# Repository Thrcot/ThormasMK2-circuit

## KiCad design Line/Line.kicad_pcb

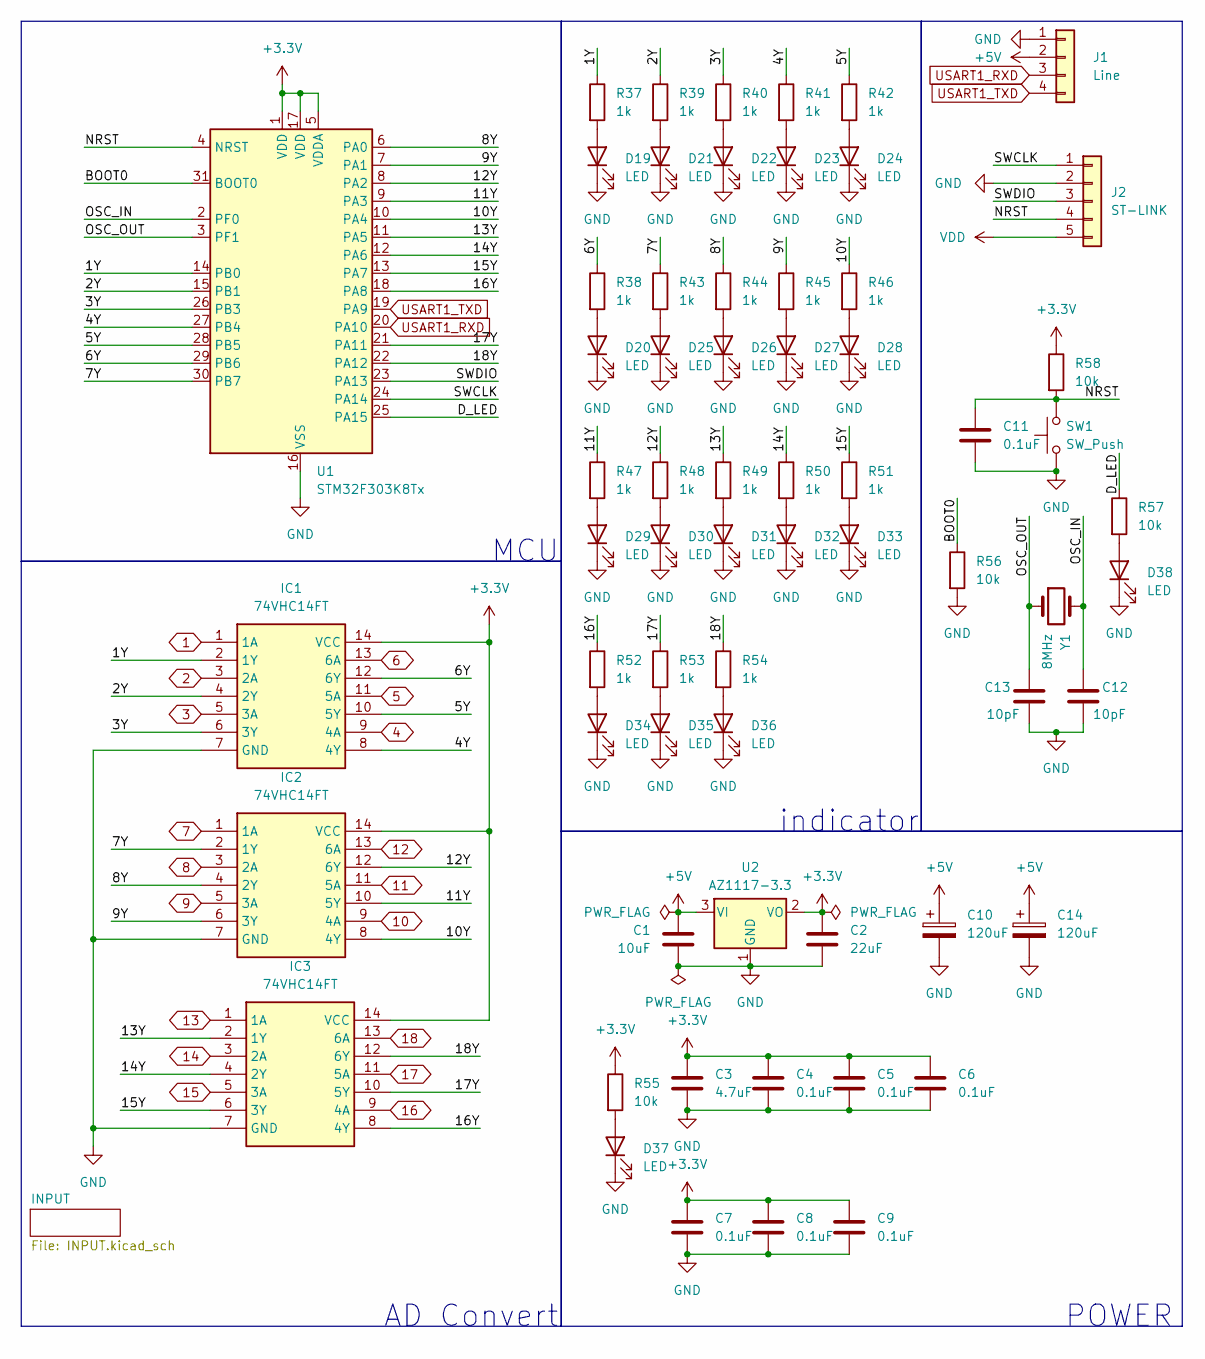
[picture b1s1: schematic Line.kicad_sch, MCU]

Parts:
C1: 10uF; C_0603_1608Metric
C2: 22uF; C_0603_1608Metric
C3: 4.7uF; C_0603_1608Metric
C4, C5, C6, C7, C8, C9, C11: 0.1uF; C_0402_1005Metric
C10, C14: 120uF; CP_Radial_D10.0mm_P5.00mm
C12, C13: 10pF; C_0402_1005Metric
D19, D20, D21, D22, D23, D24, D25, D26, D27, D28, D29, D30, D31, D32, D33, D34, D35, D36, D37, D38: LED; LED_0603_1608Metric
IC1, IC2, IC3: 74VHC14FT; SOP65P640X120-14N; Mouser Part Number 757-74VHC14FT
J1: Line; JST_XH_B4B-XH-A_1x04_P2.50mm_Vertical
J2: ST-LINK; PinHeader_1x05_P2.54mm_Vertical
R37, R38, R39, R40, R41, R42, R43, R44, R45, R46, R47, R48, R49, R50, R51, R52, R53, R54: 1k; R_0603_1608Metric
R55, R56, R57, R58: 10k; R_0603_1608Metric
SW1: SW_Push; SW_PUSH_6mm
U1: STM32F303K8Tx; LQFP-32_7x7mm_P0.8mm
U2: AZ1117-3.3; SOT-223-3_TabPin2
Y1: 8MHz; Crystal_HC49-4H_Vertical

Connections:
1: IC1.1 (1A); also elsewhere on the board
2: IC1.3 (2A); also elsewhere on the board
3: IC1.5 (3A); also elsewhere on the board
4: IC1.9 (4A); also elsewhere on the board
5: IC1.11 (5A); also elsewhere on the board
6: IC1.13 (6A); also elsewhere on the board
7: IC2.1 (1A); also elsewhere on the board
8: IC2.3 (2A); also elsewhere on the board
9: IC2.5 (3A); also elsewhere on the board
10: IC2.9 (4A); also elsewhere on the board
11: IC2.11 (5A); also elsewhere on the board
12: IC2.13 (6A); also elsewhere on the board
13: IC3.1 (1A); also elsewhere on the board
14: IC3.3 (2A); also elsewhere on the board
15: IC3.5 (3A); also elsewhere on the board
16: IC3.9 (4A); also elsewhere on the board
17: IC3.11 (5A); also elsewhere on the board
18: IC3.13 (6A); also elsewhere on the board
+3.3V: C2.1, C3.1, C4.1, C5.1, C6.1, C7.1, C8.1, C9.1, IC1.14 (VCC), IC2.14 (VCC), IC3.14 (VCC), R55.1, R58.1, U1.1 (VDD), U1.5 (VDDA), U1.17 (VDD), U2.2 (VO); also elsewhere on the board
+5V: C1.1, C10.1, C14.1, J1.2, U2.3 (VI)
/1Y: IC1.2 (1Y), R37.1, U1.14 (PB0)
/2Y: IC1.4 (2Y), R39.1, U1.15 (PB1)
/3Y: IC1.6 (3Y), R40.1, U1.26 (PB3)
/4Y: IC1.8 (4Y), R41.1, U1.27 (PB4)
/5Y: IC1.10 (5Y), R42.1, U1.28 (PB5)
/6Y: IC1.12 (6Y), R38.1, U1.29 (PB6)
/7Y: IC2.2 (1Y), R43.1, U1.30 (PB7)
/8Y: IC2.4 (2Y), R44.1, U1.6 (PA0)
/9Y: IC2.6 (3Y), R45.1, U1.7 (PA1)
/10Y: IC2.8 (4Y), R46.1, U1.10 (PA4)
/11Y: IC2.10 (5Y), R47.1, U1.9 (PA3)
/12Y: IC2.12 (6Y), R48.1, U1.8 (PA2)
/13Y: IC3.2 (1Y), R49.1, U1.11 (PA5)
/14Y: IC3.4 (2Y), R50.1, U1.12 (PA6)
/15Y: IC3.6 (3Y), R51.1, U1.13 (PA7)
/16Y: IC3.8 (4Y), R52.1, U1.18 (PA8)
/17Y: IC3.10 (5Y), R53.1, U1.21 (PA11)
/18Y: IC3.12 (6Y), R54.1, U1.22 (PA12)
/BOOT0: R56.1, U1.31 (BOOT0)
/D_LED: R57.1, U1.25 (PA15)
/NRST: C11.1, J2.4, R58.2, SW1.2, U1.4 (NRST)
/OSC_IN: C12.1, U1.2 (PF0), Y1.2
/OSC_OUT: C13.1, U1.3 (PF1), Y1.1
/SWCLK: J2.1, U1.24 (PA14)
/SWDIO: J2.3, U1.23 (PA13)
GND: C1.2, C2.2, C3.2, C4.2, C5.2, C6.2, C7.2, C8.2, C9.2, C10.2, C11.2, C12.2, C13.2, C14.2, D19.1 (K), D20.1 (K), D21.1 (K), D22.1 (K), D23.1 (K), D24.1 (K), D25.1 (K), D26.1 (K), D27.1 (K), D28.1 (K), D29.1 (K), D30.1 (K), D31.1 (K), D32.1 (K), D33.1 (K), D34.1 (K), D35.1 (K), D36.1 (K), D37.1 (K), D38.1 (K), IC1.7 (GND), IC2.7 (GND), IC3.7 (GND), J1.1, J2.2, R56.2, SW1.1, U1.16 (VSS), U1.32 (VSS), U2.1 (GND); also elsewhere on the board
unnamed: D19.2 (A), R37.2
unnamed: D20.2 (A), R38.2
unnamed: D21.2 (A), R39.2
unnamed: D22.2 (A), R40.2
unnamed: D23.2 (A), R41.2
unnamed: D24.2 (A), R42.2
unnamed: D25.2 (A), R43.2
unnamed: D26.2 (A), R44.2
unnamed: D27.2 (A), R45.2
unnamed: D28.2 (A), R46.2
unnamed: D29.2 (A), R47.2
unnamed: D30.2 (A), R48.2
unnamed: D31.2 (A), R49.2
unnamed: D32.2 (A), R50.2
unnamed: D33.2 (A), R51.2
unnamed: D34.2 (A), R52.2
unnamed: D35.2 (A), R53.2
unnamed: D36.2 (A), R54.2
unnamed: D37.2 (A), R55.2
unnamed: D38.2 (A), R57.2
USART1_RXD: J1.3, U1.20 (PA10)
USART1_TXD: J1.4, U1.19 (PA9)
VDD: J2.5

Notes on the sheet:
MCU
AD Convert
indicator
POWER

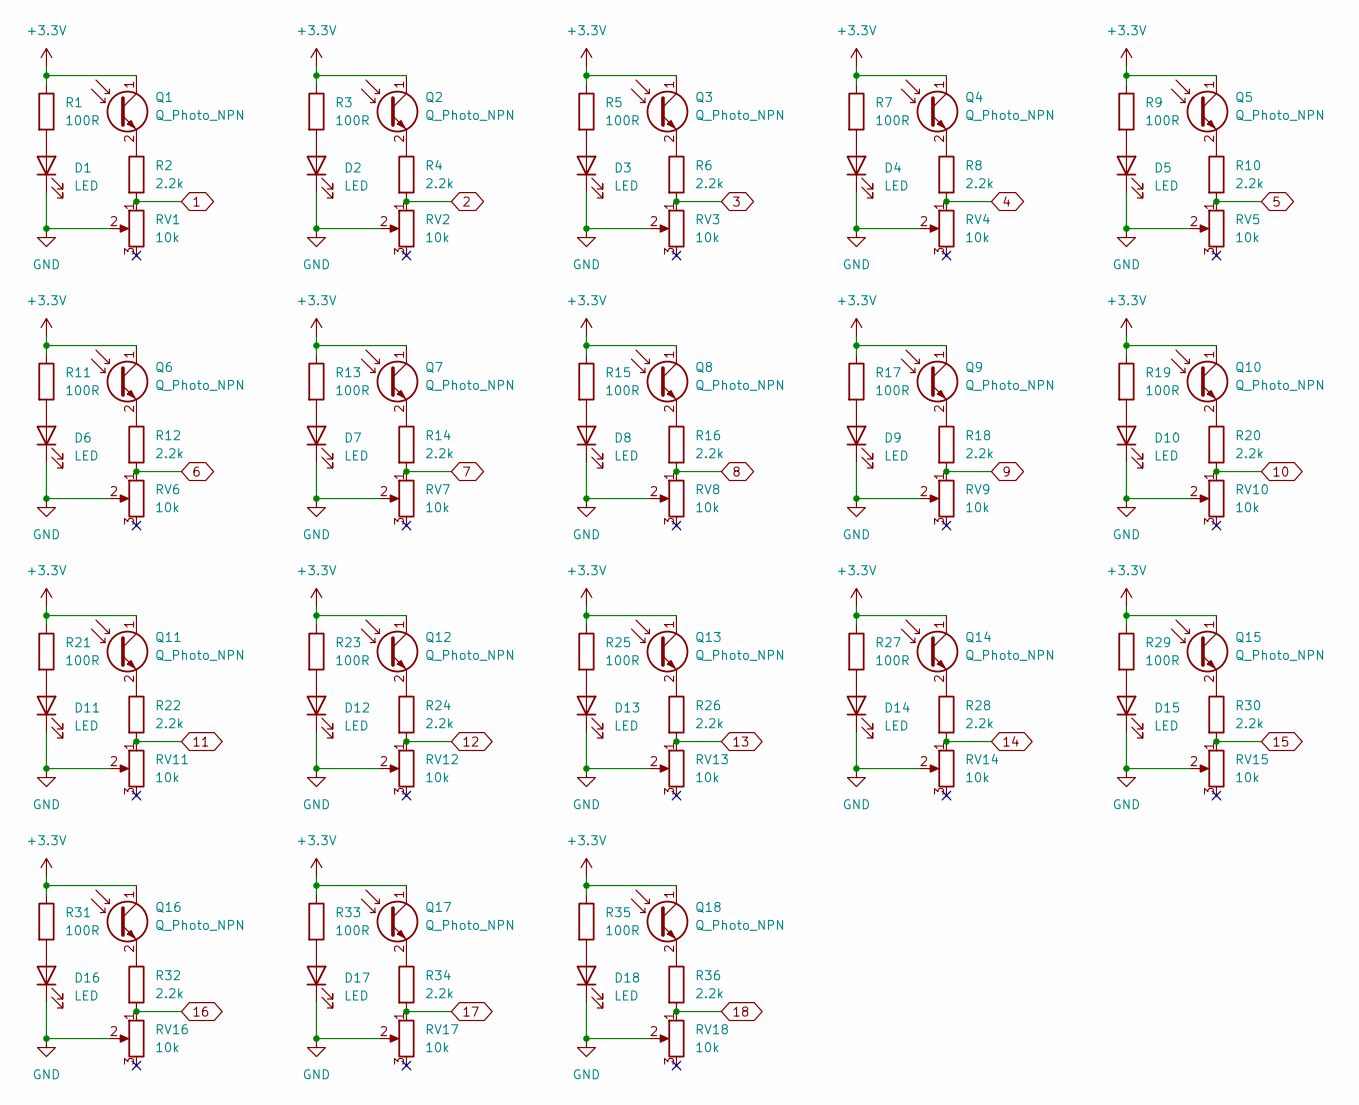
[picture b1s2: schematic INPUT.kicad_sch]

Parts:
D1, D2, D3, D4, D5, D6, D7, D8, D9, D10, D11, D12, D13, D14, D15, D16, D17, D18: LED; LED_D5.0mm
Q1, Q2, Q3, Q4, Q5, Q6, Q7, Q8, Q9, Q10, Q11, Q12, Q13, Q14, Q15, Q16, Q17, Q18: Q_Photo_NPN; LED_D3.0mm_Clear
R1, R3, R5, R7, R9, R11, R13, R15, R17, R19, R21, R23, R25, R27, R29, R31, R33, R35: 100R; R_0603_1608Metric
R2, R4, R6, R8, R10, R12, R14, R16, R18, R20, R22, R24, R26, R28, R30, R32, R34, R36: 2.2k; R_0603_1608Metric
RV1, RV2, RV3, RV4, RV5, RV6, RV7, RV8, RV9, RV10, RV11, RV12, RV13, RV14, RV15, RV16, RV17, RV18: 10k; Potentiometer_Bourns_TC33X_Vertical

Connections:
1: R2.2, RV1.1; also elsewhere on the board
2: R4.2, RV2.1; also elsewhere on the board
3: R6.2, RV3.1; also elsewhere on the board
4: R8.2, RV4.1; also elsewhere on the board
5: R10.2, RV5.1; also elsewhere on the board
6: R12.2, RV6.1; also elsewhere on the board
7: R14.2, RV7.1; also elsewhere on the board
8: R16.2, RV8.1; also elsewhere on the board
9: R18.2, RV9.1; also elsewhere on the board
10: R20.2, RV10.1; also elsewhere on the board
11: R22.2, RV11.1; also elsewhere on the board
12: R24.2, RV12.1; also elsewhere on the board
13: R26.2, RV13.1; also elsewhere on the board
14: R28.2, RV14.1; also elsewhere on the board
15: R30.2, RV15.1; also elsewhere on the board
16: R32.2, RV16.1; also elsewhere on the board
17: R34.2, RV17.1; also elsewhere on the board
18: R36.2, RV18.1; also elsewhere on the board
+3.3V: Q1.1 (C), Q2.1 (C), Q3.1 (C), Q4.1 (C), Q5.1 (C), Q6.1 (C), Q7.1 (C), Q8.1 (C), Q9.1 (C), Q10.1 (C), Q11.1 (C), Q12.1 (C), Q13.1 (C), Q14.1 (C), Q15.1 (C), Q16.1 (C), Q17.1 (C), Q18.1 (C), R1.1, R3.1, R5.1, R7.1, R9.1, R11.1, R13.1, R15.1, R17.1, R19.1, R21.1, R23.1, R25.1, R27.1, R29.1, R31.1, R33.1, R35.1; also elsewhere on the board
GND: D1.1 (K), D2.1 (K), D3.1 (K), D4.1 (K), D5.1 (K), D6.1 (K), D7.1 (K), D8.1 (K), D9.1 (K), D10.1 (K), D11.1 (K), D12.1 (K), D13.1 (K), D14.1 (K), D15.1 (K), D16.1 (K), D17.1 (K), D18.1 (K), RV1.2, RV2.2, RV3.2, RV4.2, RV5.2, RV6.2, RV7.2, RV8.2, RV9.2, RV10.2, RV11.2, RV12.2, RV13.2, RV14.2, RV15.2, RV16.2, RV17.2, RV18.2; also elsewhere on the board
unnamed: D1.2 (A), R1.2
unnamed: D2.2 (A), R3.2
unnamed: D3.2 (A), R5.2
unnamed: D4.2 (A), R7.2
unnamed: D5.2 (A), R9.2
unnamed: D6.2 (A), R11.2
unnamed: D7.2 (A), R13.2
unnamed: D8.2 (A), R15.2
unnamed: D9.2 (A), R17.2
unnamed: D10.2 (A), R19.2
unnamed: D11.2 (A), R21.2
unnamed: D12.2 (A), R23.2
unnamed: D13.2 (A), R25.2
unnamed: D14.2 (A), R27.2
unnamed: D15.2 (A), R29.2
unnamed: D16.2 (A), R31.2
unnamed: D17.2 (A), R33.2
unnamed: D18.2 (A), R35.2
unnamed: Q1.2 (E), R2.1
unnamed: Q2.2 (E), R4.1
unnamed: Q3.2 (E), R6.1
unnamed: Q4.2 (E), R8.1
unnamed: Q5.2 (E), R10.1
unnamed: Q6.2 (E), R12.1
unnamed: Q7.2 (E), R14.1
unnamed: Q8.2 (E), R16.1
unnamed: Q9.2 (E), R18.1
unnamed: Q10.2 (E), R20.1
unnamed: Q11.2 (E), R22.1
unnamed: Q12.2 (E), R24.1
unnamed: Q13.2 (E), R26.1
unnamed: Q14.2 (E), R28.1
unnamed: Q15.2 (E), R30.1
unnamed: Q16.2 (E), R32.1
unnamed: Q17.2 (E), R34.1
unnamed: Q18.2 (E), R36.1

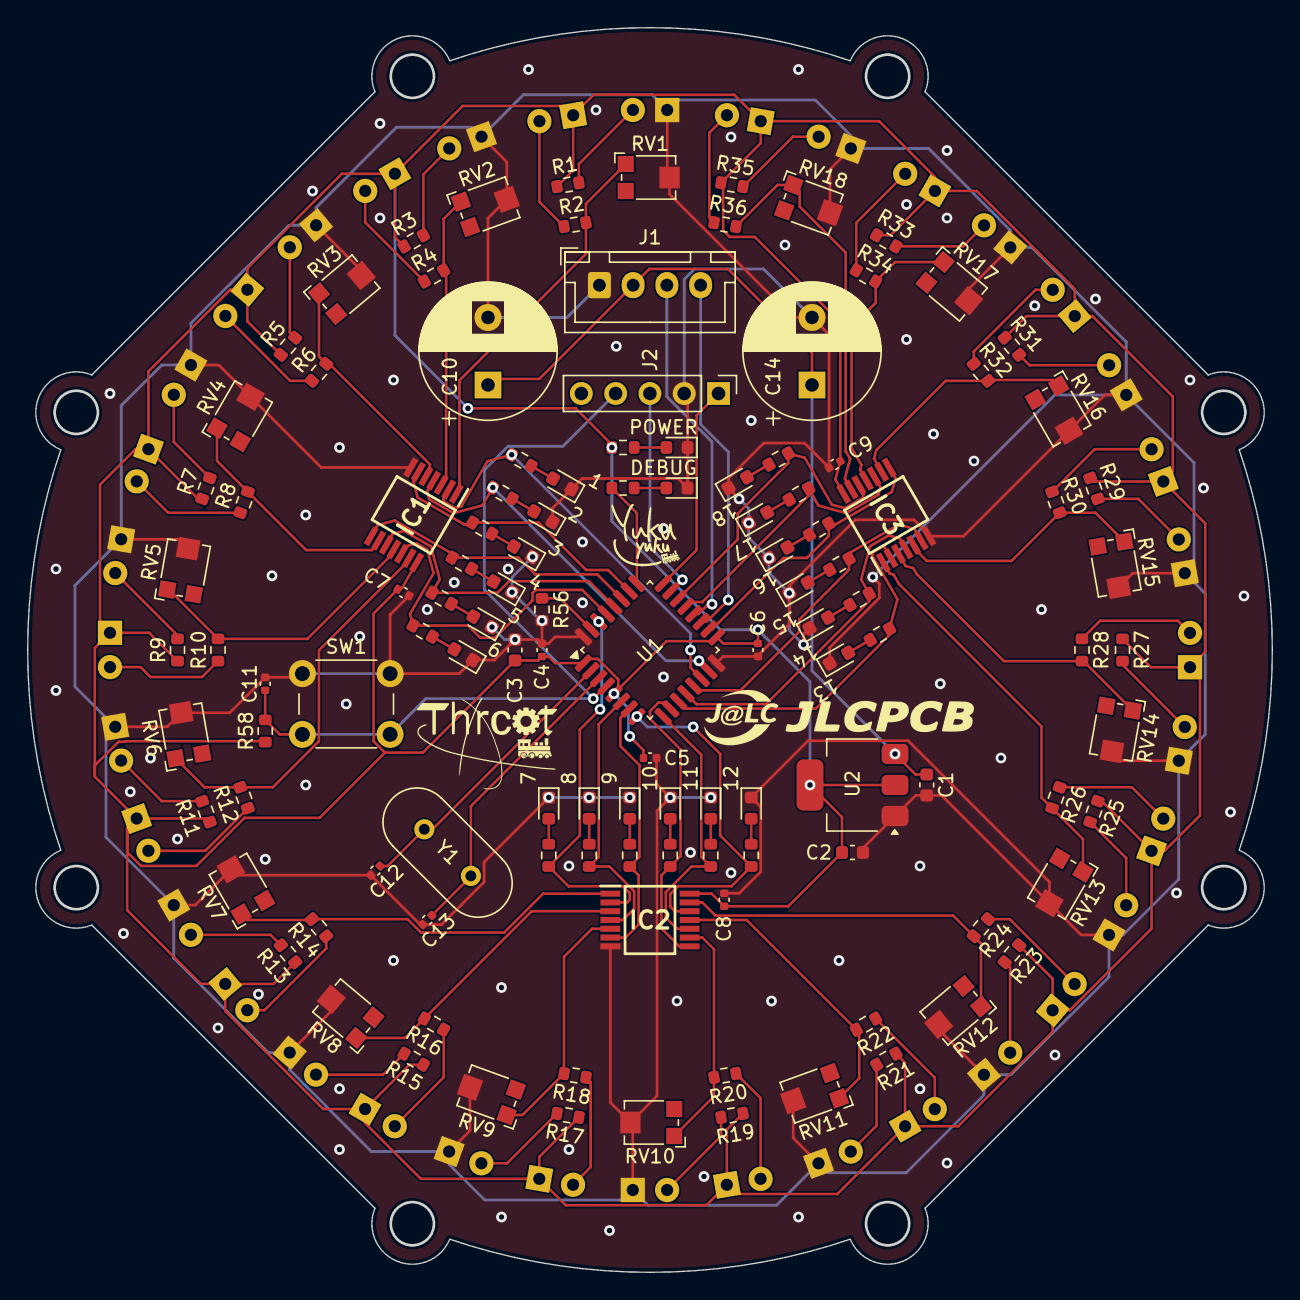
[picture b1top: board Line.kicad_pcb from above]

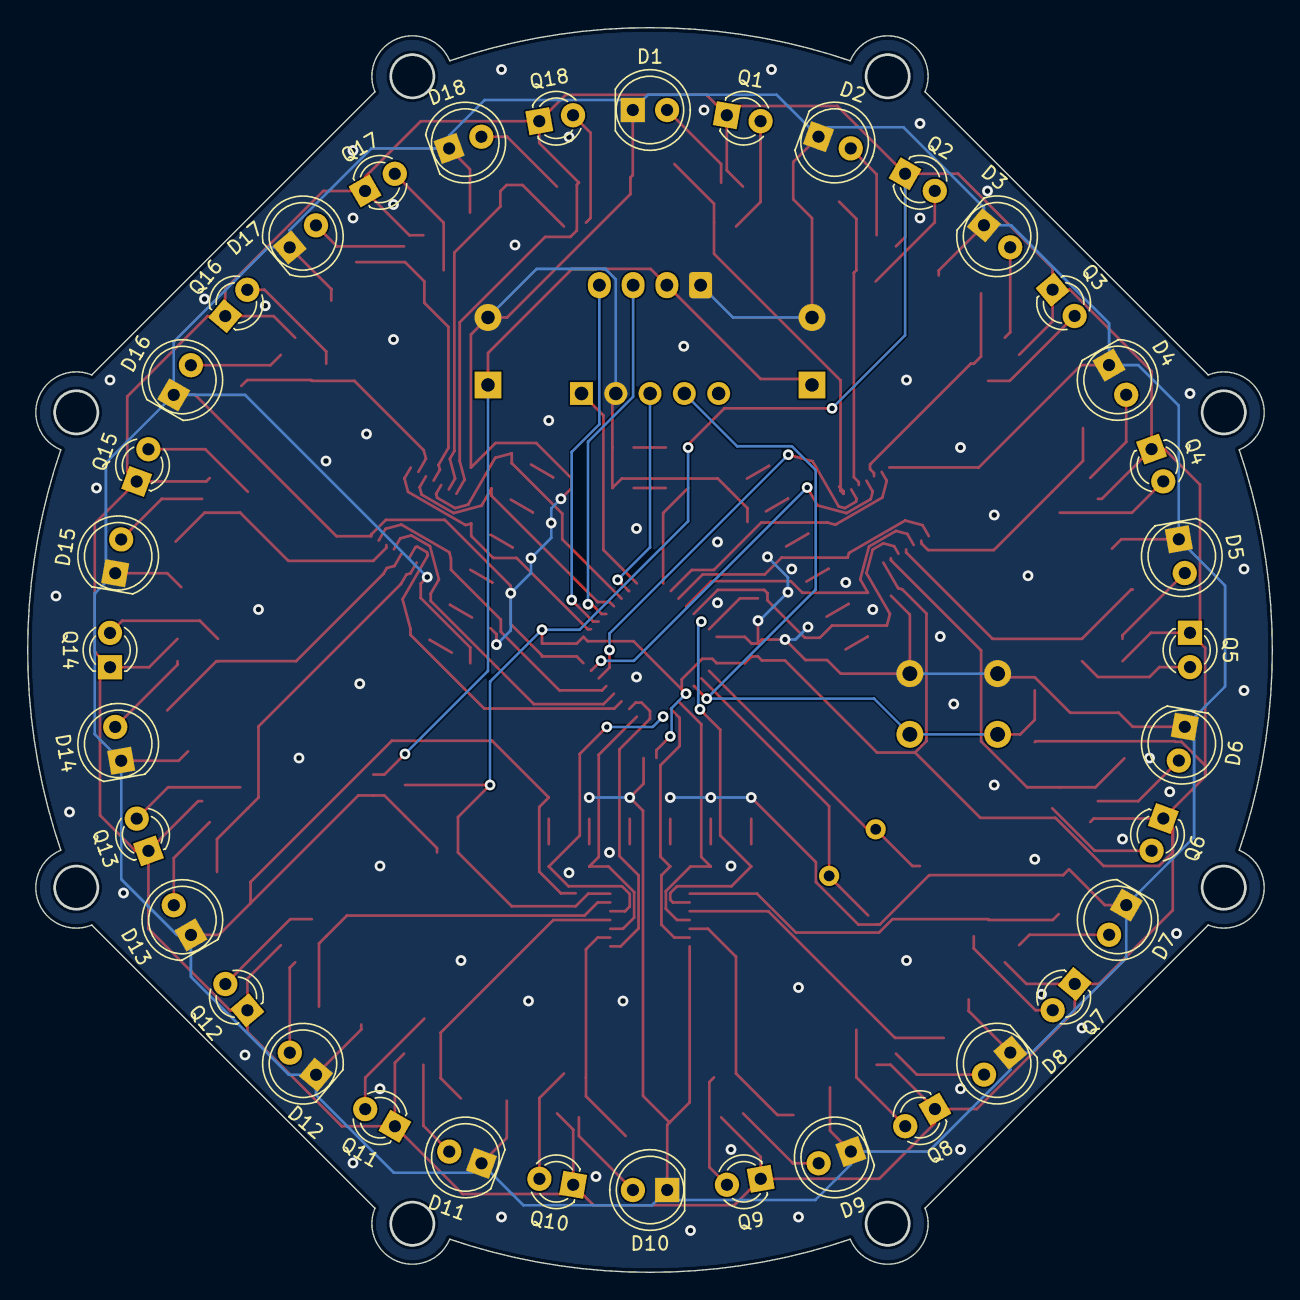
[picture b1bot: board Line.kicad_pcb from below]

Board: 2 copper layers, 92.2 x 92.2 mm, 155 parts (36 on the bottom side), 104 nets.

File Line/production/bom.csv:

Designator,Footprint,Quantity,Value,LCSC Part #
C1,0603,1,10uF,
"C10, C14",CP_Radial_D10.0mm_P5.00mm,2,120uF,
"C11, C4, C5, C6, C7, C8, C9",0402,7,0.1uF,
"C12, C13",0402,2,10pF,
C2,0603,1,22uF,
C3,0603,1,4.7uF,
"D1, D10, D11, D12, D13, D14, D15, D16, D17, D18, D2, D3, D4, D5, D6, D7, D8, D9",LED_D5.0mm,18,LED,
"D19, D20, D21, D22, D23, D24, D25, D26, D27, D28, D29, D30, D31, D32, D33, D34, D35, D36, D37, D38",0603,20,LED,
"IC1, IC2, IC3",SOP65P640X120-14N,3,74VHC14FT,
J1,JST_XH_B4B-XH-A_1x04_P2.50mm_Vertical,1,Line,
J2,PinHeader_1x05_P2.54mm_Vertical,1,ST-LINK,
"Q1, Q10, Q11, Q12, Q13, Q14, Q15, Q16, Q17, Q18, Q2, Q3, Q4, Q5, Q6, Q7, Q8, Q9",LED_D3.0mm_Clear,18,Q_Photo_NPN,
"R1, R11, R13, R15, R17, R19, R21, R23, R25, R27, R29, R3, R31, R33, R35, R5, R7, R9",0603,18,100R,
"R10, R12, R14, R16, R18, R2, R20, R22, R24, R26, R28, R30, R32, R34, R36, R4, R6, R8",0603,18,2.2k,
"R37, R38, R39, R40, R41, R42, R43, R44, R45, R46, R47, R48, R49, R50, R51, R52, R53, R54",0603,18,1k,
"R55, R56, R57, R58",0603,4,10k,
"RV1, RV10, RV11, RV12, RV13, RV14, RV15, RV16, RV17, RV18, RV2, RV3, RV4, RV5, RV6, RV7, RV8, RV9",Potentiometer_Bourns_TC33X_Vertical,18,10k,
SW1,SW_PUSH_6mm,1,SW_Push,
U1,LQFP-32_7x7mm_P0.8mm,1,STM32F303K8Tx,
U2,SOT-223-3_TabPin2,1,AZ1117-3.3,
Y1,Crystal_HC49-4H_Vertical,1,8MHz,

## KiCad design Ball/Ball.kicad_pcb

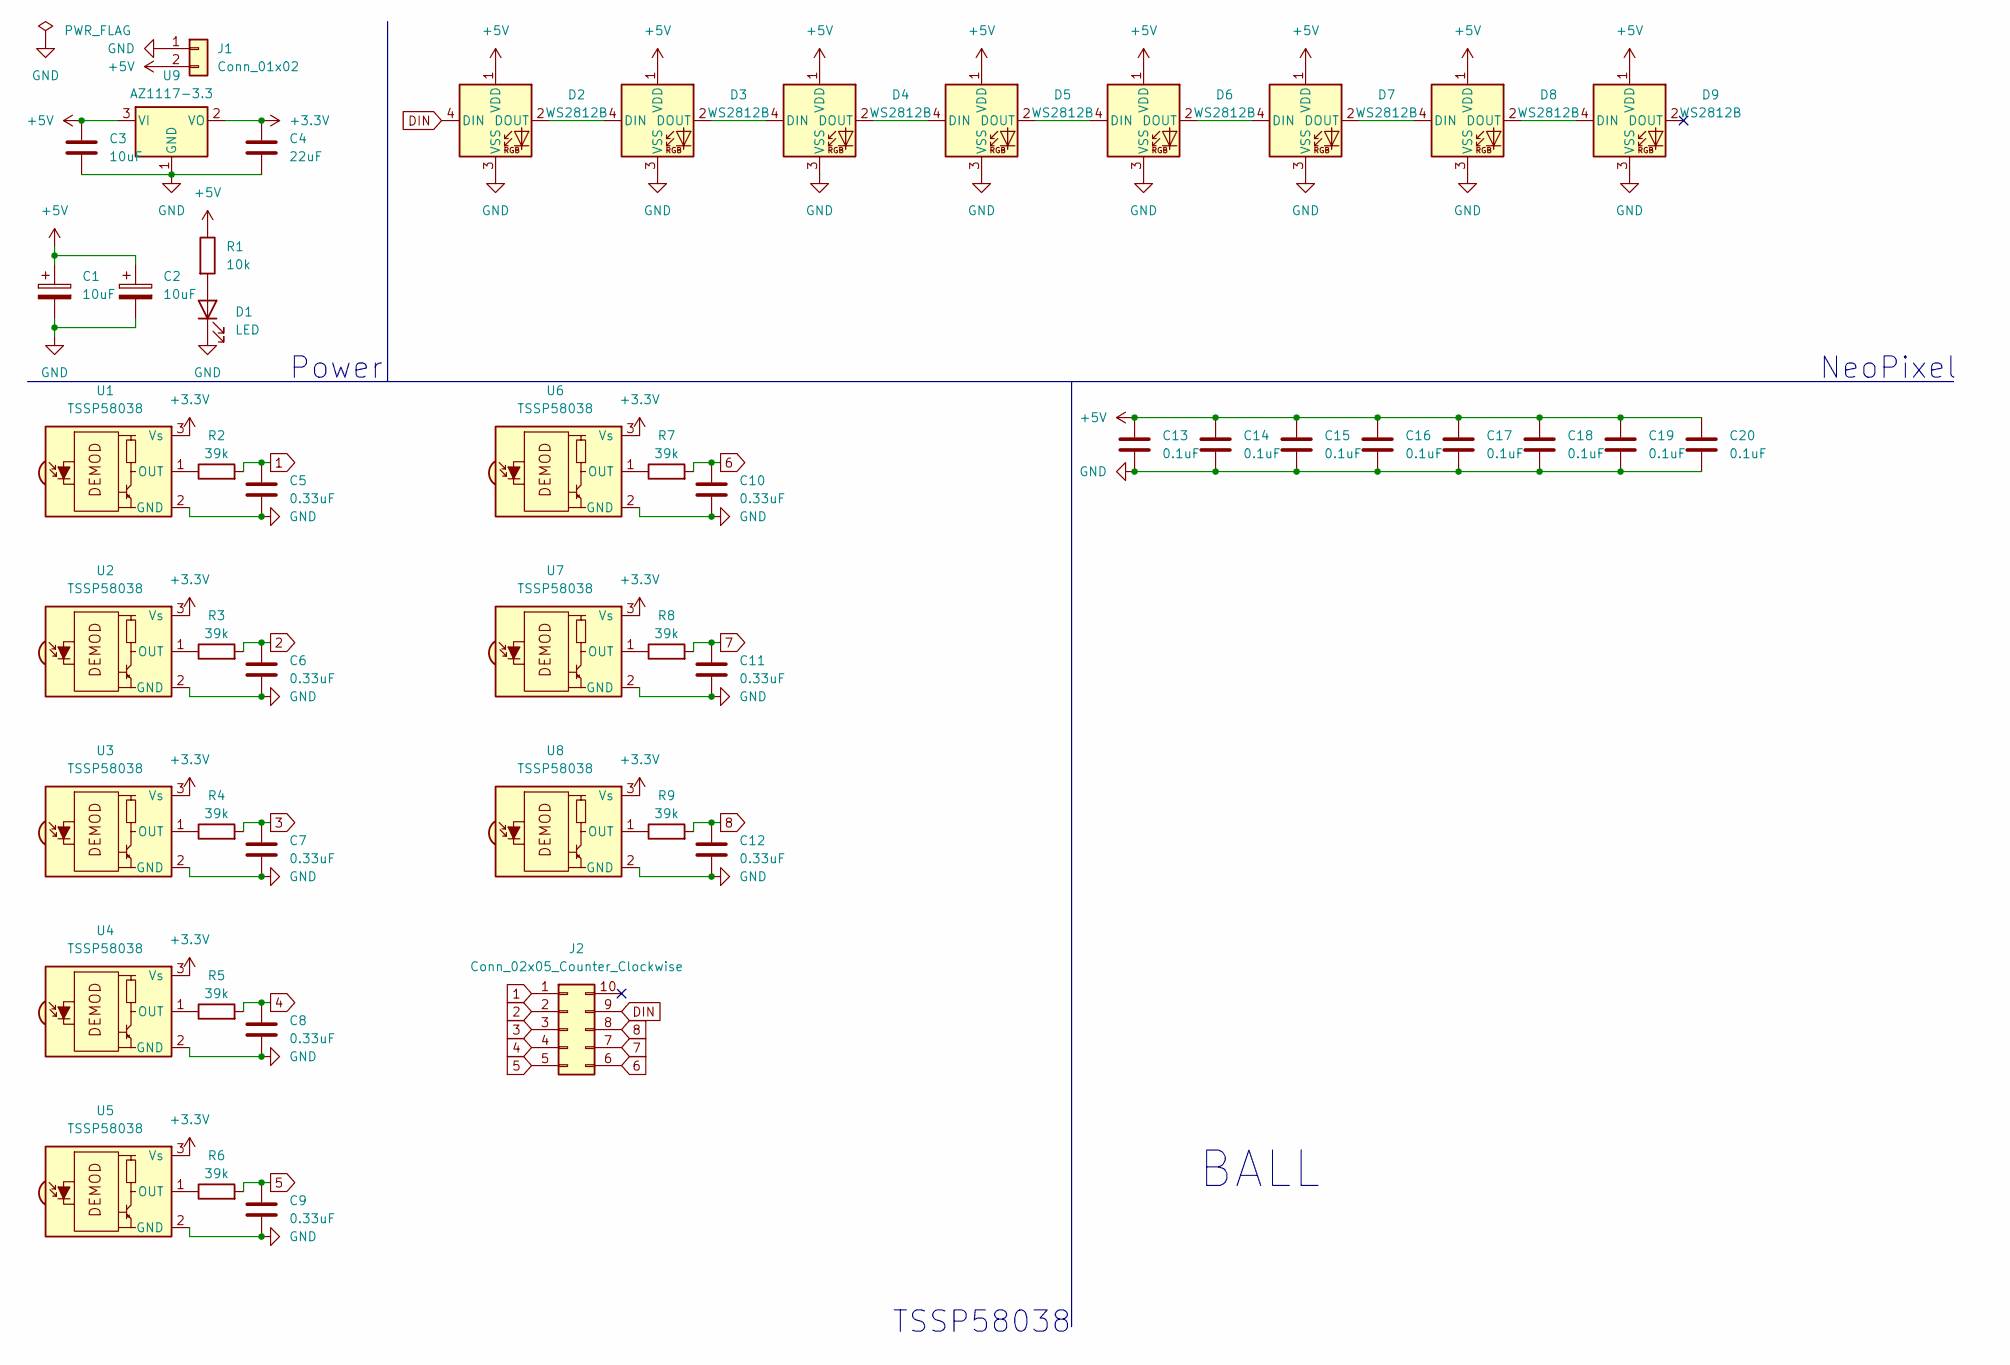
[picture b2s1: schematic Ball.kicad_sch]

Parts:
C1, C2: 10uF; CP_Radial_D8.0mm_P5.00mm
C3: 10uF; C_1206_3216Metric
C4: 22uF; C_0805_2012Metric
C5, C6, C7, C8, C9, C10, C11, C12: 0.33uF; C_0603_1608Metric
C13, C14, C15, C16, C17, C18, C19, C20: 0.1uF; C_0402_1005Metric
D1: LED; LED_0603_1608Metric
D2, D3, D4, D5, D6, D7, D8, D9: WS2812B; LED_WS2812B_PLCC4_5.0x5.0mm_P3.2mm
J1: Conn_01x02; JST_XH_S2B-XH-A_1x02_P2.50mm_Horizontal
J2: Conn_02x05_Counter_Clockwise; IDC-Header_2x05_P2.54mm_Vertical
R1: 10k; R_0603_1608Metric
R2, R3, R4, R5, R6, R7, R8, R9: 39k; R_0603_1608Metric
U1, U2, U3, U4, U5, U6, U7, U8: TSSP58038; Vishay_MINICAST-3Pin
U9: AZ1117-3.3; SOT-223-3_TabPin2

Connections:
1: C5.1, J2.1, R2.2
2: C6.1, J2.2, R3.2
3: C7.1, J2.3, R4.2
4: C8.1, J2.4, R5.2
5: C9.1, J2.5, R6.2
6: C10.1, J2.6, R7.2
7: C11.1, J2.7, R8.2
8: C12.1, J2.8, R9.2
+3.3V: C4.1, U1.3 (Vs), U2.3 (Vs), U3.3 (Vs), U4.3 (Vs), U5.3 (Vs), U6.3 (Vs), U7.3 (Vs), U8.3 (Vs), U9.2 (VO)
+5V: C1.1, C2.1, C3.1, C13.1, C14.1, C15.1, C16.1, C17.1, C18.1, C19.1, C20.1, D2.1 (VDD), D3.1 (VDD), D4.1 (VDD), D5.1 (VDD), D6.1 (VDD), D7.1 (VDD), D8.1 (VDD), D9.1 (VDD), J1.2, R1.1, U9.3 (VI)
DIN: D2.4 (DIN), J2.9
GND: C1.2, C2.2, C3.2, C4.2, C5.2, C6.2, C7.2, C8.2, C9.2, C10.2, C11.2, C12.2, C13.2, C14.2, C15.2, C16.2, C17.2, C18.2, C19.2, C20.2, D1.1 (K), D2.3 (VSS), D3.3 (VSS), D4.3 (VSS), D5.3 (VSS), D6.3 (VSS), D7.3 (VSS), D8.3 (VSS), D9.3 (VSS), J1.1, U1.2 (GND), U2.2 (GND), U3.2 (GND), U4.2 (GND), U5.2 (GND), U6.2 (GND), U7.2 (GND), U8.2 (GND), U9.1 (GND)
unnamed: D1.2 (A), R1.2
unnamed: D2.2 (DOUT), D3.4 (DIN)
unnamed: D3.2 (DOUT), D4.4 (DIN)
unnamed: D4.2 (DOUT), D5.4 (DIN)
unnamed: D5.2 (DOUT), D6.4 (DIN)
unnamed: D6.2 (DOUT), D7.4 (DIN)
unnamed: D7.2 (DOUT), D8.4 (DIN)
unnamed: D8.2 (DOUT), D9.4 (DIN)
unnamed: R2.1, U1.1 (OUT)
unnamed: R3.1, U2.1 (OUT)
unnamed: R4.1, U3.1 (OUT)
unnamed: R5.1, U4.1 (OUT)
unnamed: R6.1, U5.1 (OUT)
unnamed: R7.1, U6.1 (OUT)
unnamed: R8.1, U7.1 (OUT)
unnamed: R9.1, U8.1 (OUT)

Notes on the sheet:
Power
TSSP58038
NeoPixel
BALL

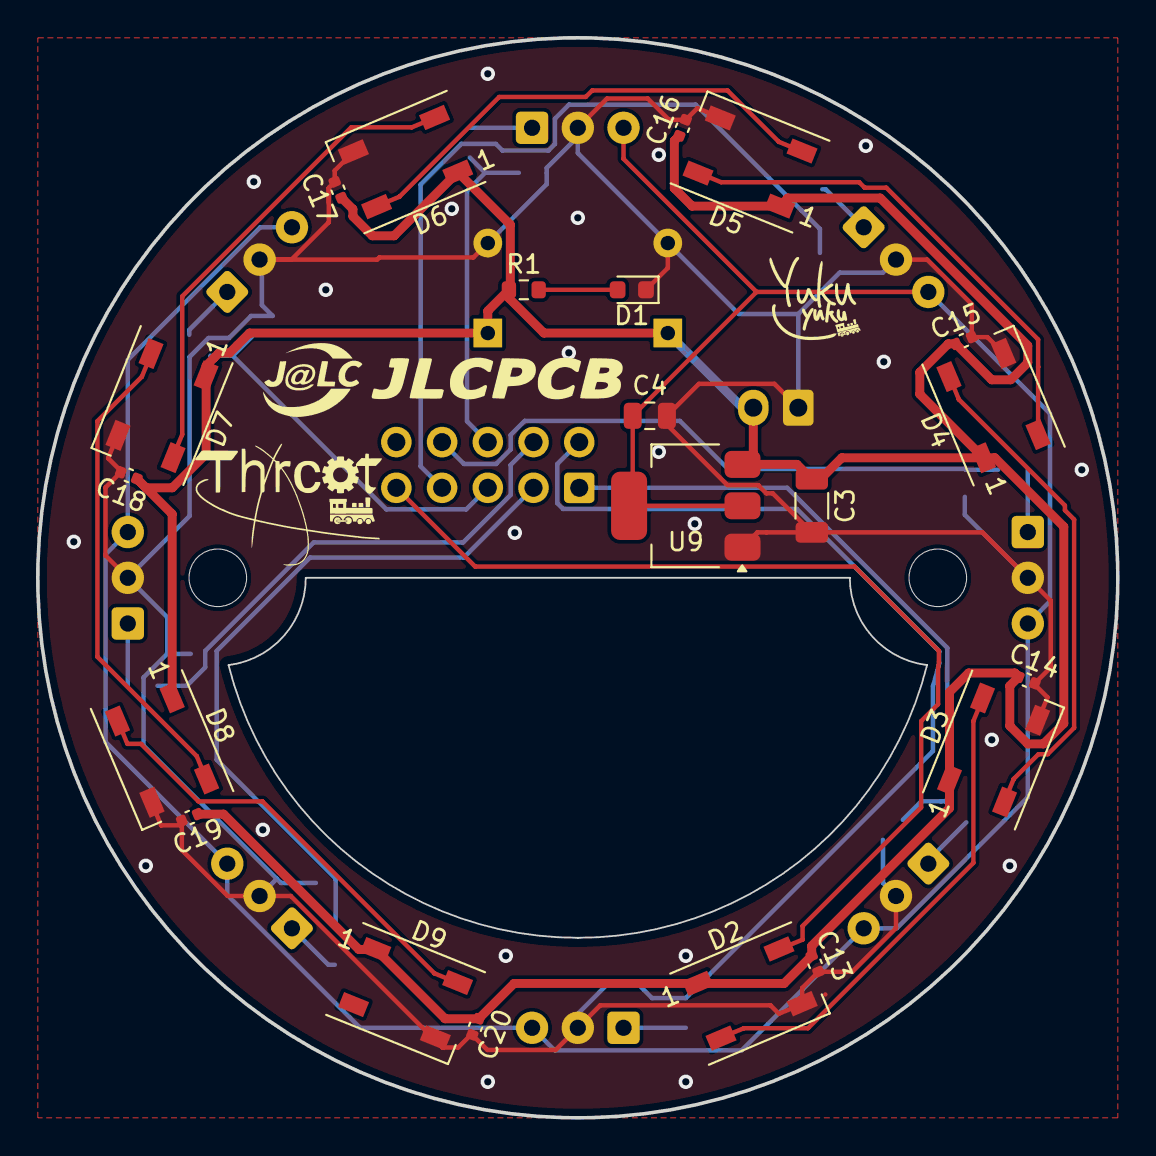
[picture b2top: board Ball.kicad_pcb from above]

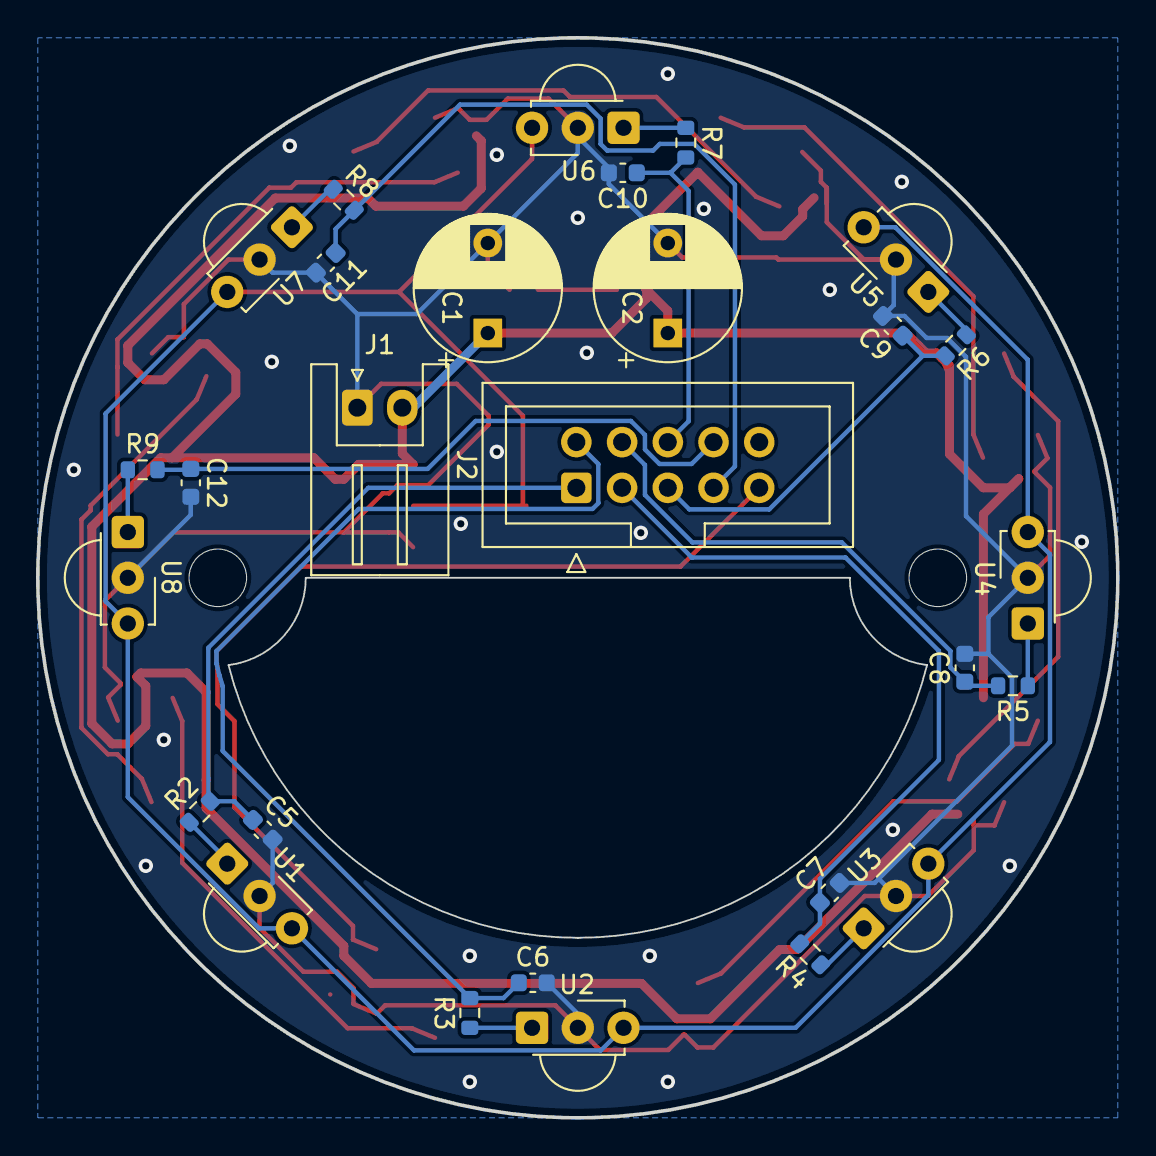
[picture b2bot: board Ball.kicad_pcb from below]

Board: 2 copper layers, 60.0 x 60.0 mm, 49 parts (28 on the bottom side), 28 nets.

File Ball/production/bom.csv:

Designator,Footprint,Quantity,Value,LCSC Part #
"C1, C2",CP_Radial_D8.0mm_P5.00mm,2,10uF,
"C10, C11, C12, C5, C6, C7, C8, C9",0603,8,0.33uF,
"C13, C14, C15, C16, C17, C18, C19, C20",0402,8,0.1uF,
C3,1206,1,10uF,
C4,0805,1,22uF,
D1,0603,1,LED,
"D2, D3, D4, D5, D6, D7, D8, D9",LED_WS2812B_PLCC4_5.0x5.0mm_P3.2mm,8,WS2812B,
J1,JST_XH_S2B-XH-A_1x02_P2.50mm_Horizontal,1,Conn_01x02,
J2,IDC-Header_2x05_P2.54mm_Vertical,1,Conn_02x05_Counter_Clockwise,
R1,0603,1,10k,
"R2, R3, R4, R5, R6, R7, R8, R9",0603,8,39k,
"U1, U2, U3, U4, U5, U6, U7, U8",Vishay_MINICAST-3Pin,8,TSSP58038,
U9,SOT-223-3_TabPin2,1,AZ1117-3.3,
